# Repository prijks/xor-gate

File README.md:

# xor-gate

This project was my first KiCad learning experience. It was inspired by [HackerBox 0039](https://www.instructables.com/HackerBox-0039-Level-Up/), which includes similar PCBs for other gates such as AND, NAND, OR and NOR. I thought a similar XOR board would be nice.

## Materials required

You will obviously need the board, which you can have manufactured using the PCB design in this project. Additionally, you will need the following:

* Four (4) 2N2222A NPN Transistors (TO-92 Package)
* Four (4) 10kk Ohm Resistors
* One (1) 1K Ohm Resistor
* One (1) 5mm LED
* Two (2) Tactile Momentary Buttons
* One (1) 2x1 Pin Header

## Assembly

The 1k Ohm resistor goes in the top of the board by VCC. Orientation doesn't matter.

The 10k Ohm resistors go in the other resistor positions. Orientation doesn't matter.

The transistors are all oriented with the flat side to the right.

LED is oriented with the short pin down (towards ground).

The buttons should only fit in one direction.

## Caveat

The board works, but this is not necessarily the best TTL XOR design, since I am not an electrical engineer.

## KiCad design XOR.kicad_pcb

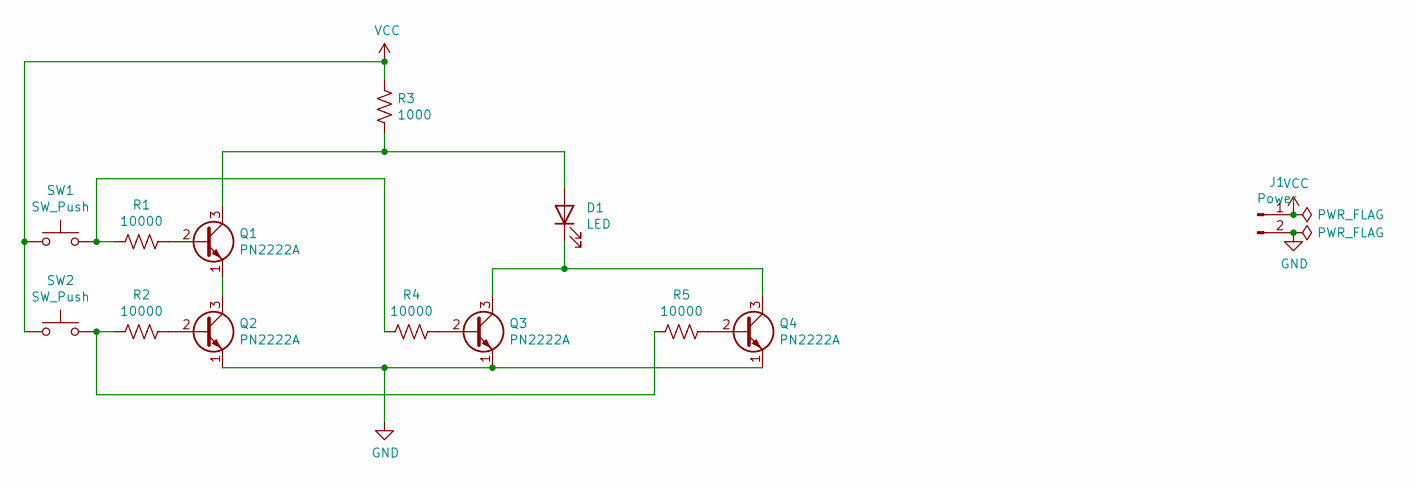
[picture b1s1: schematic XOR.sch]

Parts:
D1: LED; LED_D5.0mm
J1: Power; PinHeader_1x02_P2.54mm_Vertical
Q1, Q2, Q3, Q4: PN2222A; TO-92_Inline_Wide
R1, R2, R4, R5: 10000; R_Axial_DIN0411_L9.9mm_D3.6mm_P12.70mm_Horizontal
R3: 1000; R_Axial_DIN0411_L9.9mm_D3.6mm_P12.70mm_Horizontal
SW1, SW2: SW_Push; SW_PUSH_6mm_H5mm

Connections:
GND: J1.2, Q2.1 (E), Q3.1 (E), Q4.1 (E)
unnamed: D1.1 (K), Q3.3 (C), Q4.3 (C)
unnamed: D1.2 (A), Q1.3 (C), R3.2
unnamed: Q1.1 (E), Q2.3 (C)
unnamed: Q1.2 (B), R1.1
unnamed: Q2.2 (B), R2.1
unnamed: Q3.2 (B), R4.1
unnamed: Q4.2 (B), R5.1
unnamed: R1.2, R4.2, SW1.2
unnamed: R2.2, R5.2, SW2.2
VCC: J1.1, R3.1, SW1.1, SW2.1

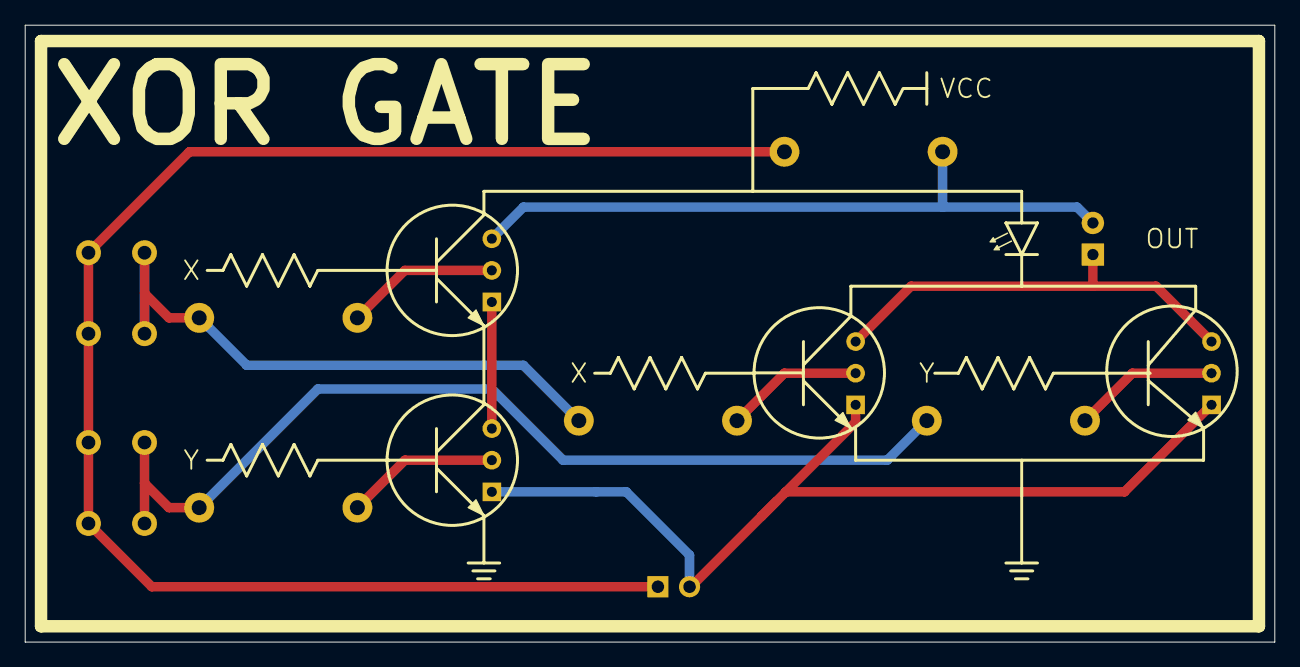
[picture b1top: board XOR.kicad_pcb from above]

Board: 2 copper layers, 100.3 x 49.5 mm, 13 parts (1 on the bottom side), 11 nets.

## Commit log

2021-07-24 Add render of PCB
